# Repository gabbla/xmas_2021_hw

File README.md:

# Xmas 2021

This is the repository that contains the xmas 2021 badge schematic and pcb.
The badge is equipped with an [STM8L101F2P3] MCU, a coin cell, a push button and
7 LEDs. There are various test point so you can play with it, if you want.

A jig programmer adapter is provided in [prog_adapter](prog_adapter). Since a
lot of PCBs were made, the adapter gave an huge help during the programming
phase: no extra pin header or soldering required.

## Hardware

The BoM has been kept as minimal as possible to reduce costs.

| Annotation | Part                  | Package | Q.ty | Note                                   |
|------------|-----------------------|---------|------|----------------------------------------|
| BT1        | BH57A-5               |         | 1    | CR1616/CR1620 battery holder           |
| C1, C3     | 100nF                 | 0603    | 2    |                                        |
| C2         | 10uF                  | 0603    | 1    |                                        |
| D1 - D7    | LED                   | 0603    | 7    | Red, Green, Blue, Orange SMD LEDs      |
| J1         | 00-9155-004-251-006   |         | 0    | Slide contact, receiver footprint only |
| R1, R2     | 4k7                   | 0603    | 2    | I2C optional pull-up                   |
| R3 - R9    | 100 - 150             | 0603    | 7    | LEDs resistor                          |
| SW1        | PTS526 SK15 SMTR2 LFS |         | 1    | User button                            |
| U1         | STM8L101F2P3          | TSSOP20 | 1    | MCU                                    |

The PCB cutout and top silk screen were traced from a PNG icon (see [credits](#credits) below) using
[svg2shenzhen], an Inkscape plugin. The source image in both PNG and SVG (traced from the PNG) can be found
in [res](res). The [svg2shenzhen] output is a KiCad library.

The resulting PCB:

## Firmware

The firmware can be found [here](https://github.com/SebastianoC94/XMAS_Tree_2021). Thanks [@SebastianoC94]!

The firmware can be flashed with any SWIM-capable probe (JLink, STLinkV2/V3).

## Credits

- [@SebastianoC94]
- KiCad
- [svg2shenzhen]
- PCB cutout traced from [this](https://www.flaticon.com/free-icon/christmas-tree_6118946) flaticon image. Artist: [Freepik](https://www.freepik.com)

[STM8L101F2P3]: https://www.st.com/en/microcontrollers-microprocessors/stm8l101f2.html
[svg2shenzhen]: https://github.com/badgeek/svg2shenzhen
[@SebastianoC94]: https://github.com/SebastianoC94

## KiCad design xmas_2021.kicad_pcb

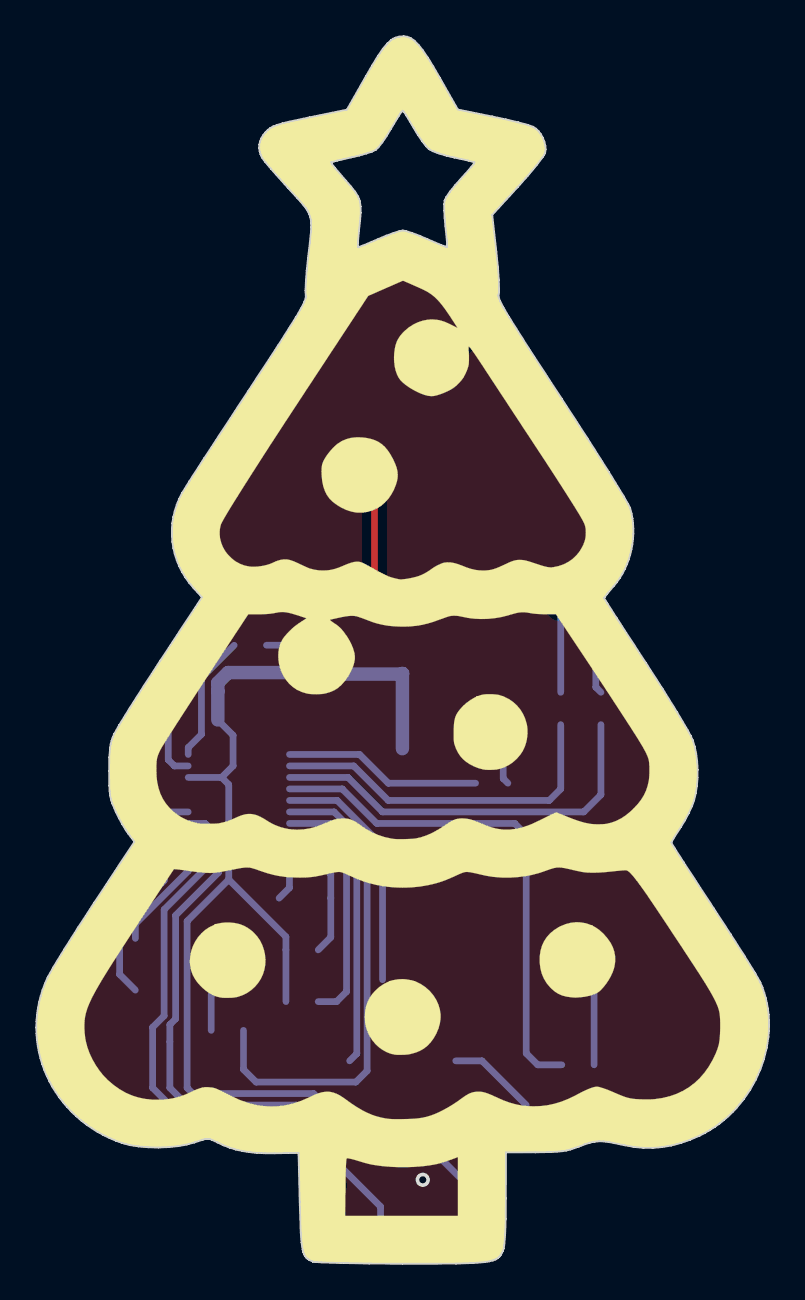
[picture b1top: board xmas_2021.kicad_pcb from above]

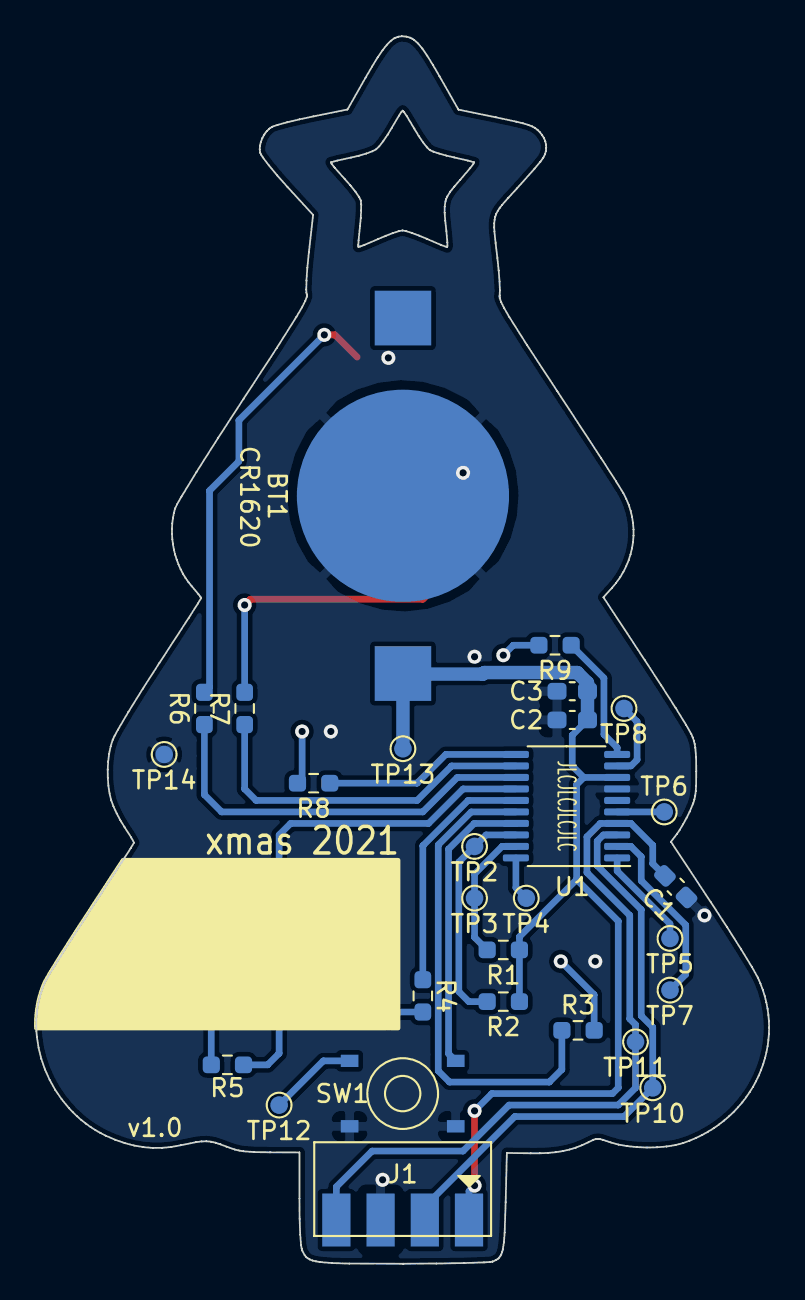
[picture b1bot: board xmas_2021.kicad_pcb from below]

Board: 2 copper layers, 41.4 x 69.4 mm, 36 parts (28 on the bottom side), 27 nets.

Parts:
BT1: CR2032; BH57A-5
C1, C3: 100n; C_0603_1608Metric_Pad1.08x0.95mm_HandSolder
C2: 10u; C_0603_1608Metric_Pad1.08x0.95mm_HandSolder
D1, D2, D3, D4, D5, D6, D7: LED; LED_0603_1608Metric_Pad1.05x0.95mm_HandSolder
J1: SWIM; swim
R1, R2: DNP; R_0603_1608Metric_Pad0.98x0.95mm_HandSolder
R3, R4, R5, R6, R7, R8, R9: R; R_0603_1608Metric_Pad0.98x0.95mm_HandSolder
Ref**: Val**; christmas-tree
SW1: User; button
TP2: I2C_DATA; TestPoint_Pad_D1.0mm
TP3: I2C_CLOCK; TestPoint_Pad_D1.0mm
TP4: USART_RX; TestPoint_Pad_D1.0mm
TP5: USART_TX; TestPoint_Pad_D1.0mm
TP6: IO1; TestPoint_Pad_D1.0mm
TP7: IO2; TestPoint_Pad_D1.0mm
TP8: IO3; TestPoint_Pad_D1.0mm
TP10: SWIM; TestPoint_Pad_D1.0mm
TP11: NRST; TestPoint_Pad_D1.0mm
TP12: USR_BTN; TestPoint_Pad_D1.0mm
TP13: VBATT; TestPoint_Pad_D1.0mm
TP14: GND; TestPoint_Pad_D1.0mm
U1: STM8L101F2P3; TSSOP-20_4.4x6.5mm_P0.65mm

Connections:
+BATT: BT1.1, C2.1, C3.1, J1.1, R1.1, R2.1, TP13.1, U1.8
/I2C_CLOCK: R1.2, TP3.1, U1.19
/I2C_DATA: R2.2, TP2.1, U1.18
/IO1: TP6.1, U1.5
/IO2: TP7.1, U1.2
/IO3: TP8.1, U1.9
/LED0: R3.1, U1.16
/LED1: R4.1, U1.15
/LED2: R5.1, U1.14
/LED3: R6.1, U1.13
/LED4: R7.1, U1.12
/LED5: R8.1, U1.11
/LED6: R9.1, U1.10
/NRST: C1.1, J1.4, TP11.1, U1.4
/SWIM: J1.2, TP10.1, U1.3
/USART_RX: TP4.1, U1.20
/USART_TX: TP5.1, U1.1
GND: BT1.2, C1.2, C2.2, C3.2, D1.1, D2.1, D3.1, D4.1, D5.1, D6.1, D7.1, J1.3, SW1.1, SW1.2, TP14.1, U1.7
unnamed: D1.2, R3.2
unnamed: D2.2, R4.2
unnamed: D3.2, R5.2
unnamed: D4.2, R6.2
unnamed: D5.2, R7.2
unnamed: D6.2, R8.2
unnamed: D7.2, R9.2
unnamed: SW1.3, U1.17
unnamed: SW1.4, TP12.1

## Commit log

2021-11-18 sch: update after hw test
2021-11-21 first version
2021-11-21 pcb: added JLC sn placeholder
2021-11-21 readme: init
2021-11-28 battery holder is now BH57A-5
2021-11-28 removed unwanted symbols
2021-12-10 prog adapter added
2021-12-28 minor fixes
2021-12-28 readme: wip
2021-12-28 tag fix
2021-12-28 added animation
2021-12-28 readme: moved tha animation on top
2021-12-28 kicad pro sync
2021-12-28 prog adapter info
2021-12-28 typo
